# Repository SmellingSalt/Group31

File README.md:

# FinalYearProject

Hello, this is the github repository for our final year project.
Clone this repo and start work on your own, try different things if you can.

The **Dataset** folder must contain all the datasets collected so far. 

The **MasterCodeOffline** folder must contain the SSVEP code and its branches.

The **Miscellaneous** folder must contain any other form of codes/ideas/links pertaining to the project.

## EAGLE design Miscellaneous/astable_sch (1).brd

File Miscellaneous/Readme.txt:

<<<<<<< HEAD
This consists of all the miscellaneous information, codes, whatever.
=======
This consists of all the miscellaneous information, codes, whatever.
>>>>>>> b7b56d9cba35e154395521e6c31a5fec55555911 232

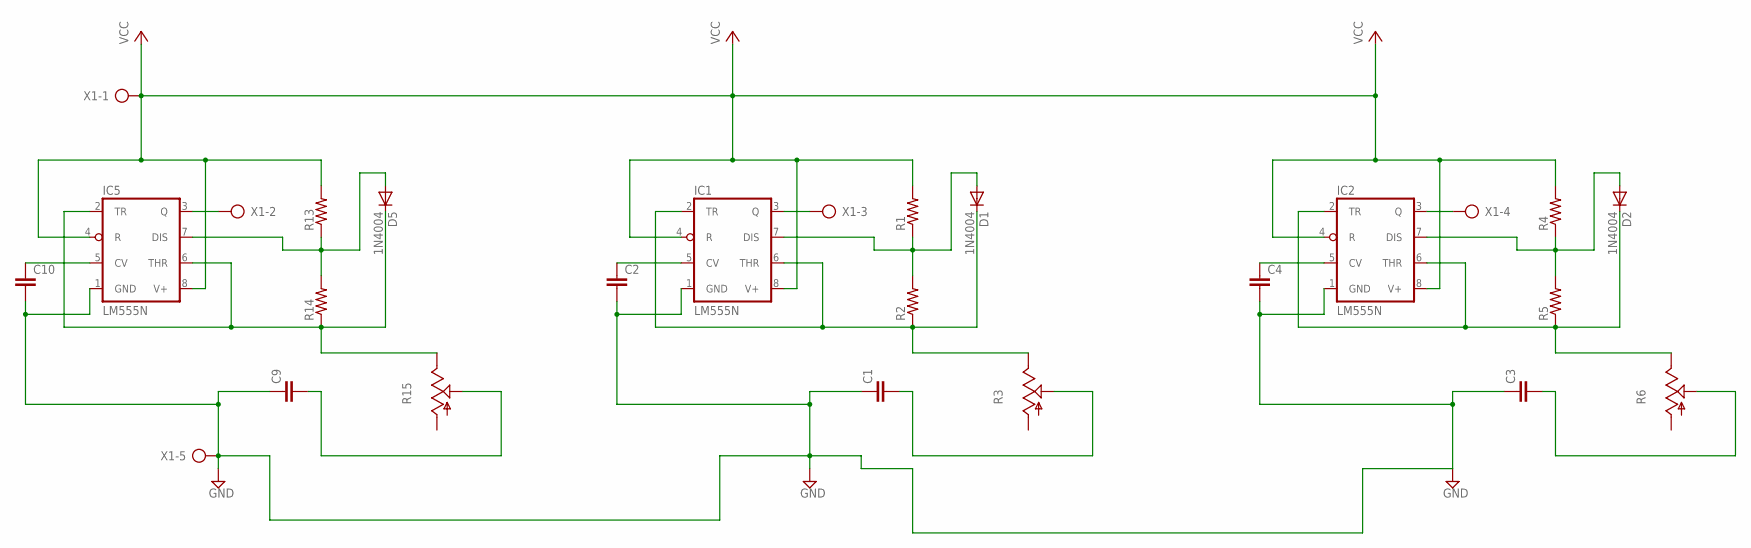
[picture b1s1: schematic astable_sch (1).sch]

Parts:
C1, C2, C3, C4, C9, C10: C-EU025-024X044; C025-024X044
D1, D2, D5: 1N4004; DO41-10
IC1, IC2, IC5: LM555N; DIL08
R1, R2, R4, R5, R13, R14: R-US_0204/7; 0204/7
R3, R6, R15: TRIM_US-B25V; B25V
X1: AK300/5

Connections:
GND: C1.1, C2.2, C3.1, C4.2, C9.1, C10.2, IC1.1 (GND), IC2.1 (GND), IC5.1 (GND), X1.5
unnamed: D1.A, IC1.7 (DIS), R1.1, R2.2
unnamed: D1.C, IC1.2 (TR), IC1.6 (THR), R2.1, R3.E
unnamed: C2.1, IC1.5 (CV)
unnamed: IC1.3 (Q), X1.3
unnamed: C1.2, R3.S
unnamed: D2.A, IC2.7 (DIS), R4.1, R5.2
unnamed: D2.C, IC2.2 (TR), IC2.6 (THR), R5.1, R6.E
unnamed: C4.1, IC2.5 (CV)
unnamed: IC2.3 (Q), X1.4
unnamed: C3.2, R6.S
unnamed: D5.A, IC5.7 (DIS), R13.1, R14.2
unnamed: D5.C, IC5.2 (TR), IC5.6 (THR), R14.1, R15.E
unnamed: C10.1, IC5.5 (CV)
unnamed: IC5.3 (Q), X1.2
unnamed: C9.2, R15.S
VCC: IC1.4 (R), IC1.8 (V+), IC2.4 (R), IC2.8 (V+), IC5.4 (R), IC5.8 (V+), R1.2, R4.2, R13.2, X1.1

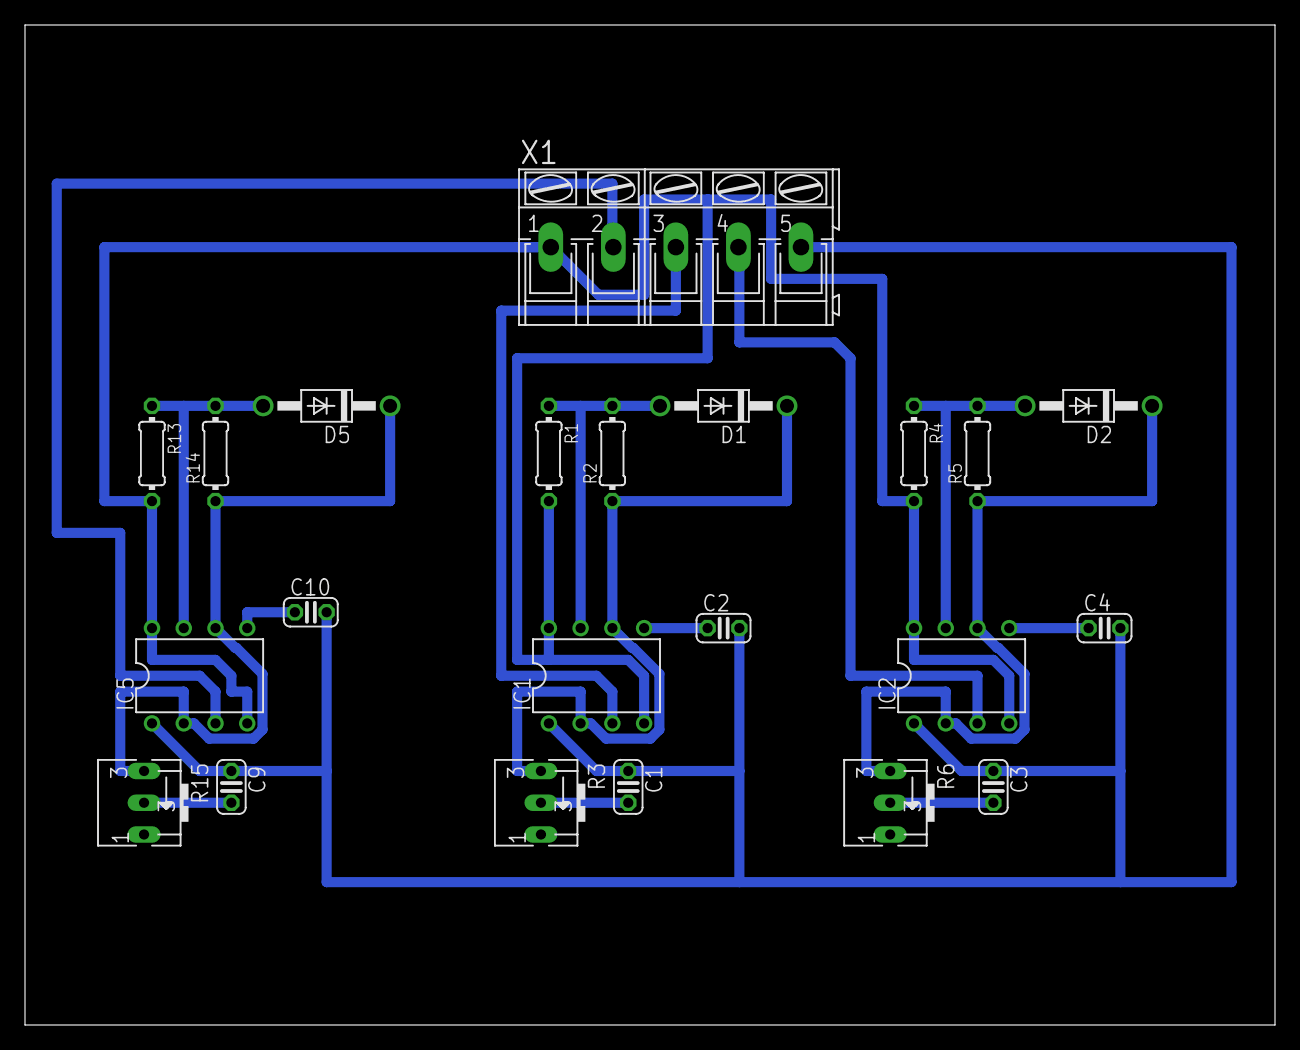
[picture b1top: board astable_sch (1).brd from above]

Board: 2 copper layers, 100.0 x 80.0 mm, 22 parts (0 on the bottom side), 17 nets.

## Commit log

2018-02-01 Copied the files
2018-02-01 Covariance matrix from X.
2018-02-01 Deleted spaces.
2018-02-01 testing
2018-02-01 Moved files
2018-02-01 Deleted a space
2018-02-01 Dataset description.
2018-02-01 Uploading small size dataset.
2018-02-01 Reimann mean of Covariance matrix.
    EEGtoCov() returns the reimann mean covariance matrix (4 x1).
    Next update the ExtEEG.m to read .gdf files one after the other and store in X.
    Note: Till now we have finished finding mean covariance of a single .gdf file.
2018-02-03 Dataset update.
    Uploading new dataset. some files are .gdf format.
2018-02-03 updating dataset
    note that we are using 4
2018-02-03 Uploading previous year's dataset. Made by seniors.
2018-02-04 added gitignore file
2018-02-05 Spelling
2018-02-06 3D Struct
    Added a function that collects EEG data from different files and stores it in a 3D struct.
    Also created a 'Training' matlab master code tha uses different functions made to help train the classifier
2018-02-06 Tweaking and testing
    Training.m is the master code which right now only stores all the EEG recordings of a single patient, in a 3D structure
    SubjectEEG.m is the function that extracts and loads multiple EEG files into one large 3D structure, in matlab.
2018-02-06 Little organisation
    Added each person's EEG sessions into a folder.
2018-02-06 Junk removal
    Deleted some junk files
2018-02-06 Folder Functions
    Added a folder named 'functions' where all the functions create for the main code should be.
2018-02-11 Covariance matrix CELL structure Computation
    EEGtoCov computes the Covariance matrix cell structure corresponding to the eeg data X cell structure.
2018-02-11 Subject mean Computation.
    Done with the Training.m program which finds the mean of a individual suject.
2018-02-11 Create led interfacing
2018-02-13 File Moving
    Created the Hardware folder and moved the code inside
2018-02-15 Tangent space
    Added a return functoin in mean to get the tangent space projection of the covariance matricies
2018-02-15 Spliting to Training and Testing
2018-02-15 Renamed to be more Readable
2018-02-15 Adjustments
    Changed the file path to the partitioned training and testing set
    Also made the variable names more readable
2018-02-15 Outlier Removal.
    Outlier removal.
    After this function the Co is nothing the covariance matrix cell structure, but with the outliers removed.
2018-02-15 DataSet Organistion
    Moved DataSets to help train and classify
2018-02-15 Algorithm 2
    Added functions to help classify and predict accuracies
2018-02-15 Optimisation
    -Csize=size(C);
    instead of doing
    ClassLnth=Csize(1);
    trials=Csize(2);
    files=Csize(3);
    I replaced it with
2018-02-15 Small adjustment
    [~,~,gdfLnth]=size(X);
    Added this line to take care of cases where only one GDF file is present
2018-02-15 Final Core Code
    Code is implemented to obtain classification results
2018-02-15 Semicolon
2018-02-16 Outlier Removal
    Finishing up the function.
2018-02-16 Testing folder
2018-02-16 Sorry for not observing.
    Had created a testing folder to do the accuracy calculations. Not needed as we are doing it in Implementation.m
2018-02-16 Optimisation
    Changes other instances of the redundant code.
    ***
    Csize=size(C);
    ClassNo=Csize(1);
    trialNo=Csize(2);
    fileNo=Csize(3);
2018-03-01 ASV Files are not needed
2018-03-01 Added New Path to training and testing
    There are errors here. I don't know why
2018-03-03 deleted unwanted thing
2018-03-15 EEG Lab Addition
2018-03-15 Moved Functions
    Moved thunctions to organise everything
2018-03-15 FIR Low Pass
    Started work on a low pass FIR Filter to pre process EEG Data
2018-03-15 Moved to Active Functions
2018-03-15 Changed Training and Testing Path
2018-03-15 Added Reference Papers
    Reference Papers to read about SSVEP Pre-processing
2018-03-15 Added Review Material
2018-03-20 LowPass Filter
    Made the lowpass filter for EEG signals, designed with 'filterDesign' tool.
2018-03-20 Comb Filter
    Designed a comb filter for 0, 7,13,21 hz
2018-03-20 High Pass Filter
    Function that passes frequencies above 21 Hz
2018-03-20 Transpose Cell
    transposes a cell of deoth 1
2018-03-20 Debug added
    Debug returns one EEG trial randomly out of the large data structure
2018-03-20 Debug
2018-03-20 PreProcessing
    Bank(X,1)
    FIRLOW(X,1)
    Performs comb and lowpass SNR Boosting, respectively
    Bank(X,0)
    FIRLOW(X,0)
    Performs comb and lowpass filtering, respectively
2018-03-20 Debug
    Debug is raw EEG data
2018-03-23 outlier removal update
    changing the Z score.
2018-03-23 Reference paper
2018-03-23 Review 4
    Added PPT Slides for review 4
2018-03-27 Name change
    Accidentally changed name of function call, reverted it here
2018-03-27 Adjustments
    Final adjustments were done here
2018-03-27 Added Main reference paper
2018-03-28 Shrinkage Covariance
    Changed to ShkCovariance because it gave better results
2018-03-28 Improved Comments
2018-03-28 Improved BPF
    Made a narrower BPF Bank to filter more cleanly
2018-03-28 Reults Folder
    Added a folder to hold various results
2018-03-28 Organising
2018-03-28 File Organisation
2018-03-28 Epoch extraction
    Not Complete, Logical error still there
2018-03-28 EEG Epoch Extraction Finished
    These functions take GDF files and arranges them as D Epochs per row, until all the samples are used up.
2018-03-28 Started Work Implementing Algorithm3
    So far, only extracts EEG segments and arranges them in a tall data structure
2018-03-28 Slight Error
    According to the comment "this runs for the no. of trials in the gdf file", it should be taking the breadth of X1, not length of X1. The length of X1 and ClassLnth(1) are the same, and so both the lo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
2018-03-28 Not using Outlier Removal here
    Not required while computing initial mean, needed only in algorithm 3
2018-03-28 Saving Variables
    The means Computed from algorithm 1 and 2 are saved so it can be used in algorithm 3
2018-03-28 Saving Variables
    Entire Workspace of Algo1 and 2 is saved so that it can be used in algorithm 3
2018-04-05 Added Timestamp
    This is so that we know when particular SSVEP has started
2018-04-05 Not important
    Not using tangent space so can be ignored
2018-04-05 Added Extra Condition
    If the matrix is null, to avoid conflict later since we can't multiply a null sized matrix with a finite sized one, this extra condition was added
2018-04-05 Not important
2018-04-05 Added function
    This function gives us the vector of preditions K
2018-04-05 Fixed Bug
    Differentiated channel size and no. of trials with bredX and bred
2018-04-05 Minor Spelling Update
2018-04-05 Added Mean
    Added the filtered Data's covariance centers
2018-04-05 Recomputed Class Mean
2018-04-05 Filtered EEG Epochs
    Split the data into 4 parts so that it can be uploaded onto github
2018-04-05 Algorithm 3
    Built a vetor of predictions for epochs
2018-04-07 Moved Dataset for ease of use
2018-04-07 Curve Classification
    Started work on curve classification
2018-04-07 Recomputed centers
    Using the same training and testing set
2018-04-07 Added more predictions
    Returning the second and third minimum detected class
2018-04-07 Work in progress
2018-04-07 Comment inendations
2018-04-09 ChangedMean
2018-04-09 Made train and test path the same
2018-04-09 Outlier Removal work
2018-04-11 Kalunga's code
    i got the online curve based code to work, and uploading it.
2018-04-12 Improvements
    Using different datasets and means.
2018-04-12 Retard Mean
    Added a simple way of computing centroid and using that as the initial value for the mean calculator. With that, the new means were computed and saved
2018-04-12 IIR filters
    Added Chebyshev and Elliptic IIR filters. These are significantl faster and somehow help give better results
2018-04-12 Cov Seemed to gove better results
2018-04-12 SNR Boosting seems to work. Not just normal filtering, which is depressing
2018-04-12 Bug Fix
    Added null cell handling capabilities
2018-04-12 Revert "IIR filters"
    This reverts commit 8b7ed440cd4d9887d1b118415c3bcece30f6dfea.
2018-04-12 Revert "Revert "IIR filters""
    This reverts commit e32cf5f564133a76690f84d1ee810d069c8b315e.
2018-04-12 IIR filters
2018-04-12 Changed training and testing paths
2018-04-12 Results
    Saving our new results
2018-04-12 Just ran it once
2018-04-13 Implemented New Filtering Approach
    The entire EEG Epoch is filtered according to which class it blongs and the second harmonic is also considered.
2018-04-13 Modified to include higher harmonics
2018-04-13 Kalunga's bandpass filter
2018-04-13 Improved to handle outliers
    This is done by ignoring matricies with all zeros
2018-04-13 increased tiolerance for computational speed
2018-04-13 Modified to implement all changes made today
2018-04-14 Add files via upload
    astable pcb layout
2018-04-14 Added fils to path
2018-04-14 Deleted Unwanted Files
    Old files were deleted and the large mat file containing filtered epochs was also deleted since it was filtered with an fir filter that gave poor results.
2018-04-14 PlainEEG2Cov
    This function just converts EEG Epochs to covariance matrices, no filtering done before hand.
2018-04-14 New mean is used
2018-04-14 Offline Algorithm Split
    The Implementation file is just a .m file that calls the offline functions, the plot function and deplays results. Various parameters can be adjusted here as well.
2018-04-14 No filtering is done here
    Filtering can be done if needed, but it isn't right now
2018-04-14 Moved Function
2018-04-14 Added Comments
2018-04-16 Fixed the PCB design
2018-04-16 Added Thresholding function
2018-04-17 Added gerber files for PCB printing
2018-04-17 Project abstract added
2018-04-18 Added Epoch Predictions
2018-04-18 Used Frobinious norm better
2018-04-18 Gerber Files
2018-04-18 Algorithm 3 Completed till Prediction
2018-04-19 Algorithm 3 crudely done. Confusion matricies implemented for offline
2018-04-20 Results for algorithm 3
2018-04-20 Updated the PCB Design
2018-04-25 gui working
2018-04-26 Algorithm 3 work and little bit of offline stuff
2018-04-26 Banner work and reviewStuff
2018-04-26 reset button for gui.
    i thought i had pushed this version.
    try all cases which were giving errors.
2018-04-26 checking all
2018-04-26 Confusion matrix
    Including confusion matrix plot for gui
2018-04-27 Trying to fix Online
2018-04-27 Fixed Confusion
    Was using the outlier mean instead of normal mean
2018-04-27 ofline working
    gui working for offline only
2018-04-27 only offline gui
2018-04-27 Added Mela
2018-05-04 Added Mela PPT
2018-05-20 Testing different frequencies for fun
2018-05-20 Organised References
2018-05-20 All class results
2018-05-20 Cyton datasheet
2018-05-20 Datasheet for 555 timer
    Added it in a 7z file because github refused to send the pdf noramlly
2018-05-20 Add files via upload
    Added it into a 7z archive since it is refusing to add the pdfs
2018-05-20 Project report
    checking
2018-05-20 555 datasheet
2018-05-21 Added the final project report
2018-06-12 Added GUI snapshot in results
2018-06-12 PPT for external review
2018-06-12 User manual for external review
2019-06-20 Added Covariance toolbox from Barchant here
